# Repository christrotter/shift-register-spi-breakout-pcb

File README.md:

# Overview
Tested and working as of 20240403! \o/

A simple? breakout board that provides 32 matrix pins (_16 row and 16 column_) over SPI - using only 6 MCU pins!
Designed for and tested in QMK - requires a custom matrix.  Expects you to be using ROW2COL diode orientation.

This document includes:
- Understanding shift registers (_rather extensive_)
- Matrix-inator PCB notes
- Matrix-inator schematic detail
- Sample code

There's also a [STEP file](/matrix-inator-rev2.step) for testing fitment on your models.

*-inate your keyboard matrix with the Matrix-inator!*

# Implementation notes
- The code examples are QMK-centric and utilize Chibios bits and bobs
- The latch header is redundant - **should always be connected ("enable latch")**.  If there's a future rev I will remove it.

# Why not 74HC165 shift registers?
There are 74HC589 supply issues, why not use the 74HC165 shift register?  Because *the 165 cannot share the SPI bus*, and QMK only allows you - at present - to utilize a single SPI bus.  You could use the 165 if you also included a tri-state buffer (e.g. 74HC1G125-Q100).  The 589 has that built-in.

# Usage
After soldering/hooking this into your keyboard, you'll need to add the custom matrix code to your QMK keyboard.

Between the [QMK docs](https://docs.qmk.fm/#/custom_matrix?id=custom-matrix) and this readme, you should have enough to get off the ground.

#### Connection
You can use the included 2x4 2.54mm pin header arrangement (_fits up to JST-XH headers_), or a [VIK-format 12-pin@0.5mm pitch FPC cable](https://github.com/sadekbaroudi/vik)
- _Power_: GND, 3.3V
- _Any GPIO_: Row CS, Col CS, Latch
- _SPI_: Clock/MISO/MOSI from the same SPI bus
- _rows and cols_: 2.54mm headers, do what you want here.

#### PCBA (PCB assembly)
If you want to order this, the gerbers are included in the latest [Github release](https://github.com/christrotter/shift-register-spi-breakout-pcb/releases/latest).

I seem to recall there being a silly part showing up that shouldn't have been (_like a logo or something_), but everything important came through.

Headers not part of the BOM, only the complicated and fiddly stuff.

#### Additonal parts you'll need
See the latest [Github release](https://github.com/christrotter/shift-register-spi-breakout-pcb/releases/latest) if you need all the parts.
- (_optional_) some flavour of 2.54mm-spaced headers
- 12-pin @ 0.5mm pitch FPC cable of sufficient length and a keyboard with a VIK port
  - (_or_) 2x 4-pin 2.54mm headers
- M3 hardware or some way of mounting the pcb to your model

#### Latch header notes
There's a 3-pin header labeled **Enable Latch**.

> *It will need to have pins 2 & 3 connected for the latch to work.* 

This is a development leftover.  Future revisions will not have it.

# Understanding shift registers
In order to understand shift registers, it's very important to understand how QMK's matrix scanning works.  And, of course, to understand that, you need to read their docs:
- https://docs.qmk.fm/#/understanding_qmk
- https://docs.qmk.fm/#/how_keyboards_work
- https://docs.qmk.fm/#/how_a_matrix_works

This doc is my simplification of the topic.

> **NOTE**: for the sake of illustration, you can use the idea that HIGH = "pin has voltage" and LOW = "pin is grounded". 

## Matrix scanning, tl;dr: 
1. Start matrix scan
2. Loop over each row pin.  on each loop, set this row pin HIGH (_all others LOW_) and then check **ALL** col pins for a reciprocal HIGH.
3. Build a `new_matrix_maybe` object with the result of each row iteration
4. Compare `live_matrix` with `new_matrix_maybe` - if differences, replace `live_matrix` with `new_matrix_maybe`
5. End matrix scan loop
(_and now QMK does everything else_)

> Have you ever looked at the QMK console messages for 'scan rate'?  Well that number is how many times per second the above matrix scan runs (_simplifying_).

> **NOTE**: I use the term 'row pin' in this document only to keep things simple - QMK and shift registers don't work the same way as if you had GPIOs configured as row pins.

### why ROW2COL and not COL2ROW?
I have been working on integrating the Cyboard flex-pcb system into my latest build, and Cyboard is ROW2COL.  I'm sure the design could be refactored to handle any config method.  Indeed, if you use `direct pin` (_where the switches connect to ground_) you can have an even simpler shift register and matrix design.

If you're used to COL2ROW, it's, for all intents and purposes, identical, just flip rows & cols around.

## Pseudo matrix scan code
This is (_mostly_) not real code.
```c
bool matrix_scan_custom(matrix_row_t current_matrix[]) {
    static matrix_row_t temp_matrix[ROWS_COUNT] = {0};
    for (uint8_t row = 0; row < (ROWS_COUNT); row++) {
        set_row_high(row_pin);              // this row pin is set HIGH; any keypresses will show as HIGH on col pins
        cycle_latch_pin(latch_pin);         // prepares the col shift registers for data shipping; shift register magic
        col_state = spi_receive(col_pin);   // ship col state from shift register into the MCU as col_state
        new_matrix_maybe[row] = col_state;  // update this row of the new_matrix_maybe object with the returned col state
    }
    bool matrix_has_changed = compare_matrix(new_matrix_maybe, live_matrix);
    if (matrix_has_changed) {
        update_active_matrix(new_matrix_maybe);
    }
    return matrix_has_changed;
}
```

## Shift register magic explained
> Obviously shift registers are not magic and are completely understandable - I use the word 'magic' as an entertaining literary device.  Covering all of the detail is just too much scope for this doc.  If I can understand it, you can, too!

There are two types of registers being used here:
- 74HC589: get the HIGH/LOW state of the data pins and return via SPI ([74HC589 datasheet](https://www.onsemi.com/pdf/datasheet/mc74hc589a-d.pdf))
- 74HC595: set the data pins to a HIGH/LOW state as per instructions sent via SPI ([74HC595 datasheet](https://www.onsemi.com/pdf/datasheet/mc74hc595a-d.pdf))

The shift registers each have 8 "data" pins and a bunch of SPI/functionality pins.  
- The 589 reads 8 bits of data from the data pins in parallel, and then ships them out serially.
- The 595 takes 8 bits of data serially and applies it to the data pins in parallel.

Said another way, one accepts data from our code (_595_), the other provides data for our code (_589_).

Remember that there are no perfect solutions, and you're always making tradeoffs.  Recall we have a GPIO constraint...the shift registers get us more "GPIO" at the cost of complication.  That complication comes in the form of a parallel->serial->parallel flow.

- "Hay, row_shift_register, set a row pin to HIGH, please"
- "Okay, while that row is HIGH; col_shift_register, check all your pins - any HIGH?"
(_repeat for every row pin_)

Consider the matrix sketch above...instead of using GPIOs to send the signals to rows/cols, we use magical shift registers.

While there are some nuances for handling resets and the like - for keyboard applications you endlessly loop over rows, so no need for resets or anything fancy on the row_shift_registers.  But, the col_shift_registers handle ordered data...and if you handle the data incorrectly, your matrix results are sporadic at best.

So you need to understand a tiny bit about the 589 shift registers.

Simply put - the data we need is stored in the `data latch`.  To retrieve it via SPI, we need to tell the register to transfer it from the `data latch` into the `shift register`, which has a small amount of memory for serial operations.  Once in the next 'serial transfer' part of the clock cycling, the data in the `shift register` will be pulled out over SPI.

> Remember, the 595 works on effectively the same principles, just the reverse flow.

### Deep magicks
Each shift register has 8 bits (_1 byte_) - the data pins are digital, 0 or 1 - so you can understand what is going on in your digital matrix (_HIGH/LOW_) by polling your shift registers with sets/gets (_layman's terms_).

### for each row pin
> **NOTE**: CS pins on registers are normally HIGH.  You set them LOW to activate them.

> **NOTE**: The flow graphics illustrate how a 589 register works.  A 595 is exactly the same picture, just mirrored.

1. Set `row_cs` LOW; the rows register is now the active SPI device
2. Send the data packet telling the register which pin to set HIGH (`spi_transmit`)
3. Set `row_cs` HIGH; we are done with the rows register, so de-select it
4. Set the `latch` HIGH; the 589 register transfers current pin data from latch to register
5. Set the `latch` LOW; register cannot do data transfer while latch is HIGH
6. Set the `col_cs` LOW - the register will start transferring data over SPI
7. Get the data packet that will tell us which col pin is HIGH (`spi_receive`)
8. Set the `col_cs` HIGH - we are done with the cols register, so de-select it

And now consider the 589 data flow mentioned above...

## even more depth
...is something I won't get into.  Suffice to say that the registers function with a lot of clock timing and conditions available based on what is HIGH and what is LOW.

The matrix code, Kicad files, and part datasheets provide the rest of the puzzle.

A very important feature of the design are the 10k resistor arrays/networks that pull down the col pins to ground.  If you fail to implement this you will get super random/repeating responses.  How do I know this?

### it's complicated
The order of operations is determined by the timing diagram.  That sentence makes me sound like an elite who knows more than you.  _lies.  deception._

# Matrix-inator notes

## For the DIY-er
If you want to incorporate shift registers into your PCB, highly advise you do the following...
- Read the datasheets, carefully, twice, then thrice.
- Remember that pcb manufacturers have tolerances.  Abide by them and err on the generous side.
- The pull-down effect of the 10k resistor network is non-negotiable.  Floating signal is a guarantee, not a maybe.  Floating signal means your board does not work.
- Remember that decoupling caps need to be as close as possible to their device, and the current should flow through the cap trace into the device.

## Performance
It's worth noting that if you use the full 16 rows you will not have a very performant keyboard - scan rate drops to **1100**.  Still usable as a keyboard, but you won't have a ton of CPU overhead for other features.

## PCB details
- M3 mounts; 65mm center-to-center
- The shift registers are only available as extended parts from JLC (_extra fees_)
- 2.54mm spacing on all pin footprints
- Row/col pins designed for 4x 8-pin JST-XH 2.54 headers
- Normal 2.54mm pin headers also work fine
- Two-layer board; ground pour on both sides tied together with vias

## VIK module certification

| Category                | Classification          | Response           |
| ----------------------- | ----------------------- | ------------------ |
| FPC connector           | Required                | :heavy_check_mark: |
| Breakout pins           | Recommended             | :heavy_check_mark: |
| Uses: SPI               | Optional                | :heavy_check_mark: |
| SPI used for SPI only   | Strongly recommended    | :heavy_check_mark: |
| Uses: I2C               | Optional                | :x:                |
| I2C used for I2C only   | Strongly Recommended    | :x:                |
| I2C pull ups            | Required                | N/A                |
| Uses: RGB               | Optional                | :x:                |
| Uses: Extra GPIO 1      | Optional                | :heavy_check_mark: |
| Uses: Extra GPIO 2      | Optional                | :heavy_check_mark: |
| Standard PCB Size/Mount | Strongly recommended    | :x:                |

## Pins
- ROW_CS - trigger to enable sending bits to the Row 74HC595 shift registers
- COL_CS - trigger enable reading bits from the Col 74HC589 shift registers
- LATCH_CS - trigger to prep all Col 74HC589 shift registers for data retrieval
- SPI: crucial that you use SPI pins on the same SPI bus
  - Clock: all SPI devices need this
  - MOSI: ROW shift registers are sent data from the MCU
  - MISO: COL shift registers return data to the MCU
- 3V3, GND - expects +3.3v and a ground

## Schematics

# Sample code
This will undoubtedly get improved, but this is enough to get you off the ground and using the Matrix-inator.

## info.json
Bits you'll need in `keyboard/info.json`:
```json
    "diode_direction": "ROW2COL",
    "matrix_pins": {
        "custom_lite": true,
        "rows": ["NO_PIN", "NO_PIN", "NO_PIN", "NO_PIN", "NO_PIN", "NO_PIN"],
        "cols": ["NO_PIN", "NO_PIN", "NO_PIN", "NO_PIN", "NO_PIN", "NO_PIN", "NO_PIN", "NO_PIN", "NO_PIN", "NO_PIN", "NO_PIN"]
      },
    "layouts": {
        "LAYOUT": {
            "layout": [
                {"matrix": [5, 0], "x": 0, "y": 0},
                {"matrix": [5, 1], "x": 1, "y": 0},
                etc
        }
    },
```

## config.h
Bits you'll need in `keyboard/config.h`:

For figuring out which SPI GPIO to use, section 1.4.3 here: https://datasheets.raspberrypi.com/rp2040/rp2040-datasheet.pdf
```c
// SPI configuration
#define SPI_MATRIX_DIVISOR 16
#define SPI_MODE 0
#define SPI_DRIVER SPID1 // you might change this
// GPIO config for main SPI config needs to match up with the SPI bus you are using
#define SPI_SCK_PIN  GPxx // e.g. SPI0 SCK
#define SPI_MOSI_PIN GPxx // e.g. SPI0 TX (Master Out, Slave In)
#define SPI_MISO_PIN GPxx // e.g. SPI0 RX (Master In, Slave Out)
// GPIO config for CS/latch pins can be any GPIO
#define SPI_MATRIX_LATCH_PIN GPxx
#define SPI_MATRIX_CHIP_SELECT_PIN_ROWS GPxx
#define SPI_MATRIX_CHIP_SELECT_PIN_COLS GPxx
// custom matrix config
#define MATRIX_COLS_SHIFT_REGISTER_COUNT 2
#define MATRIX_ROWS_SHIFT_REGISTER_COUNT 2
#define ROWS_COUNT 12 // this can be replaced w. array_size or something?
#define ROWS { \
    0b0000000000000001, \
    0b0000000000000010, \
    0b0000000000000100, \
    0b0000000000001000, \
    0b0000000000010000, \
    0b0000000000100000, \
    0b0000000001000000, \
    0b0000000010000000, \
    0b0000000100000000, \
    0b0000001000000000, \
    0b0000010000000000, \
    0b0000100000000000, \
} // this makes up the magic of the 'message' we send to the 595 register
```

## rules.mk
For `keyboard/rules.mk`:
```
SRC += matrix.c
```

## halconf.h
Bits you'll need in `keyboard/halconf.h`:

```c
#define HAL_USE_SPI TRUE
#define SPI_USE_WAIT TRUE
#define SPI_SELECT_MODE SPI_SELECT_MODE_PAD
```

## mcuconf.h
Bits you'll need in `keyboard/mcuconf.h`:

You might use SPI0?
```c
#undef RP_SPI_USE_SPI1
#define RP_SPI_USE_SPI1 TRUE
```

## matrix.c
This file goes in: `keyboard/keymap/map/` (_I think it might actually be meant to go in the keymap dir?_)

Actual working code.  (_mostly tested as of this writing_)
```c
// Copyright 2018-2022 Nick Brassel (@tzarc)
// Copyright 2020-2023 alin m elena (@alinelena, @drFaustroll)
// Copyright 2023 Stefan Kerkmann (@karlk90)
// Copyright 2023 (@burkfers)
// SPDX-License-Identifier: GPL-3.0-or-later

#include "quantum.h"
#include "spi_master.h"

static const uint16_t row_values[ROWS_COUNT] = ROWS;
static const pin_t latch_pin = SPI_MATRIX_LATCH_PIN;

void matrix_init_custom(void) {
    setPinOutput(SPI_MATRIX_CHIP_SELECT_PIN_COLS);
    writePinHigh(SPI_MATRIX_CHIP_SELECT_PIN_COLS);
    setPinOutput(SPI_MATRIX_CHIP_SELECT_PIN_ROWS);
    writePinHigh(SPI_MATRIX_CHIP_SELECT_PIN_ROWS);
    setPinOutput(latch_pin);
    writePinLow(latch_pin);
    spi_init();
}

static inline void write_to_rows(uint16_t value) {
    uint8_t message[2] = {(uint8_t)(value & 0xFF), (value >> 8) & 0xFF}; // cut 0xABCD into {0xAB, 0xCD}
    spi_start(SPI_MATRIX_CHIP_SELECT_PIN_ROWS, true, SPI_MODE, SPI_MATRIX_DIVISOR);
    spi_transmit(message, 2);
    spi_stop();
}

// /**
//  * @brief Helper function to wait until a pin  has reached the wanted target
//  * state. This only works for Push-Pull pins with enabled input stage.
//  */
static void __time_critical_func(write_and_wait_for_pin)(pin_t pin, uint8_t target_state) {
    writePin(pin, target_state);
    rtcnt_t start = chSysGetRealtimeCounterX();
    rtcnt_t end   = start + MS2RTC(REALTIME_COUNTER_CLOCK, 20);
    while (chSysIsCounterWithinX(chSysGetRealtimeCounterX(), start, end)) {
        if (readPin(pin) == target_state) {
            return;
        }
    }
}

bool matrix_scan_custom(matrix_row_t current_matrix[]) {
    static matrix_row_t temp_matrix[ROWS_COUNT] = {0};
    
    for (uint8_t row = 0; row < (ROWS_COUNT); row++) {
        uint8_t temp_col_receive[MATRIX_COLS_SHIFT_REGISTER_COUNT] = {0};
        uint16_t temp_col_state;

        write_to_rows(row_values[row]);

        // get the shift registers to move data from latch to register
        write_and_wait_for_pin(latch_pin, 1);
        write_and_wait_for_pin(latch_pin, 0);

        // read the cols shift register contents over serial
        spi_start(SPI_MATRIX_CHIP_SELECT_PIN_COLS, true, SPI_MODE, SPI_MATRIX_DIVISOR);
        spi_receive((uint8_t*)temp_col_receive, MATRIX_COLS_SHIFT_REGISTER_COUNT);
        spi_stop();

        temp_col_state = temp_col_receive[0] | (temp_col_receive[1] << 8);
        temp_matrix[row] = temp_col_state;
    }
    bool matrix_has_changed = memcmp(current_matrix, temp_matrix, sizeof(temp_matrix)) != 0;
    if (matrix_has_changed) {
        memcpy(current_matrix, temp_matrix, sizeof(temp_matrix));
    }
    return matrix_has_changed;
}
```

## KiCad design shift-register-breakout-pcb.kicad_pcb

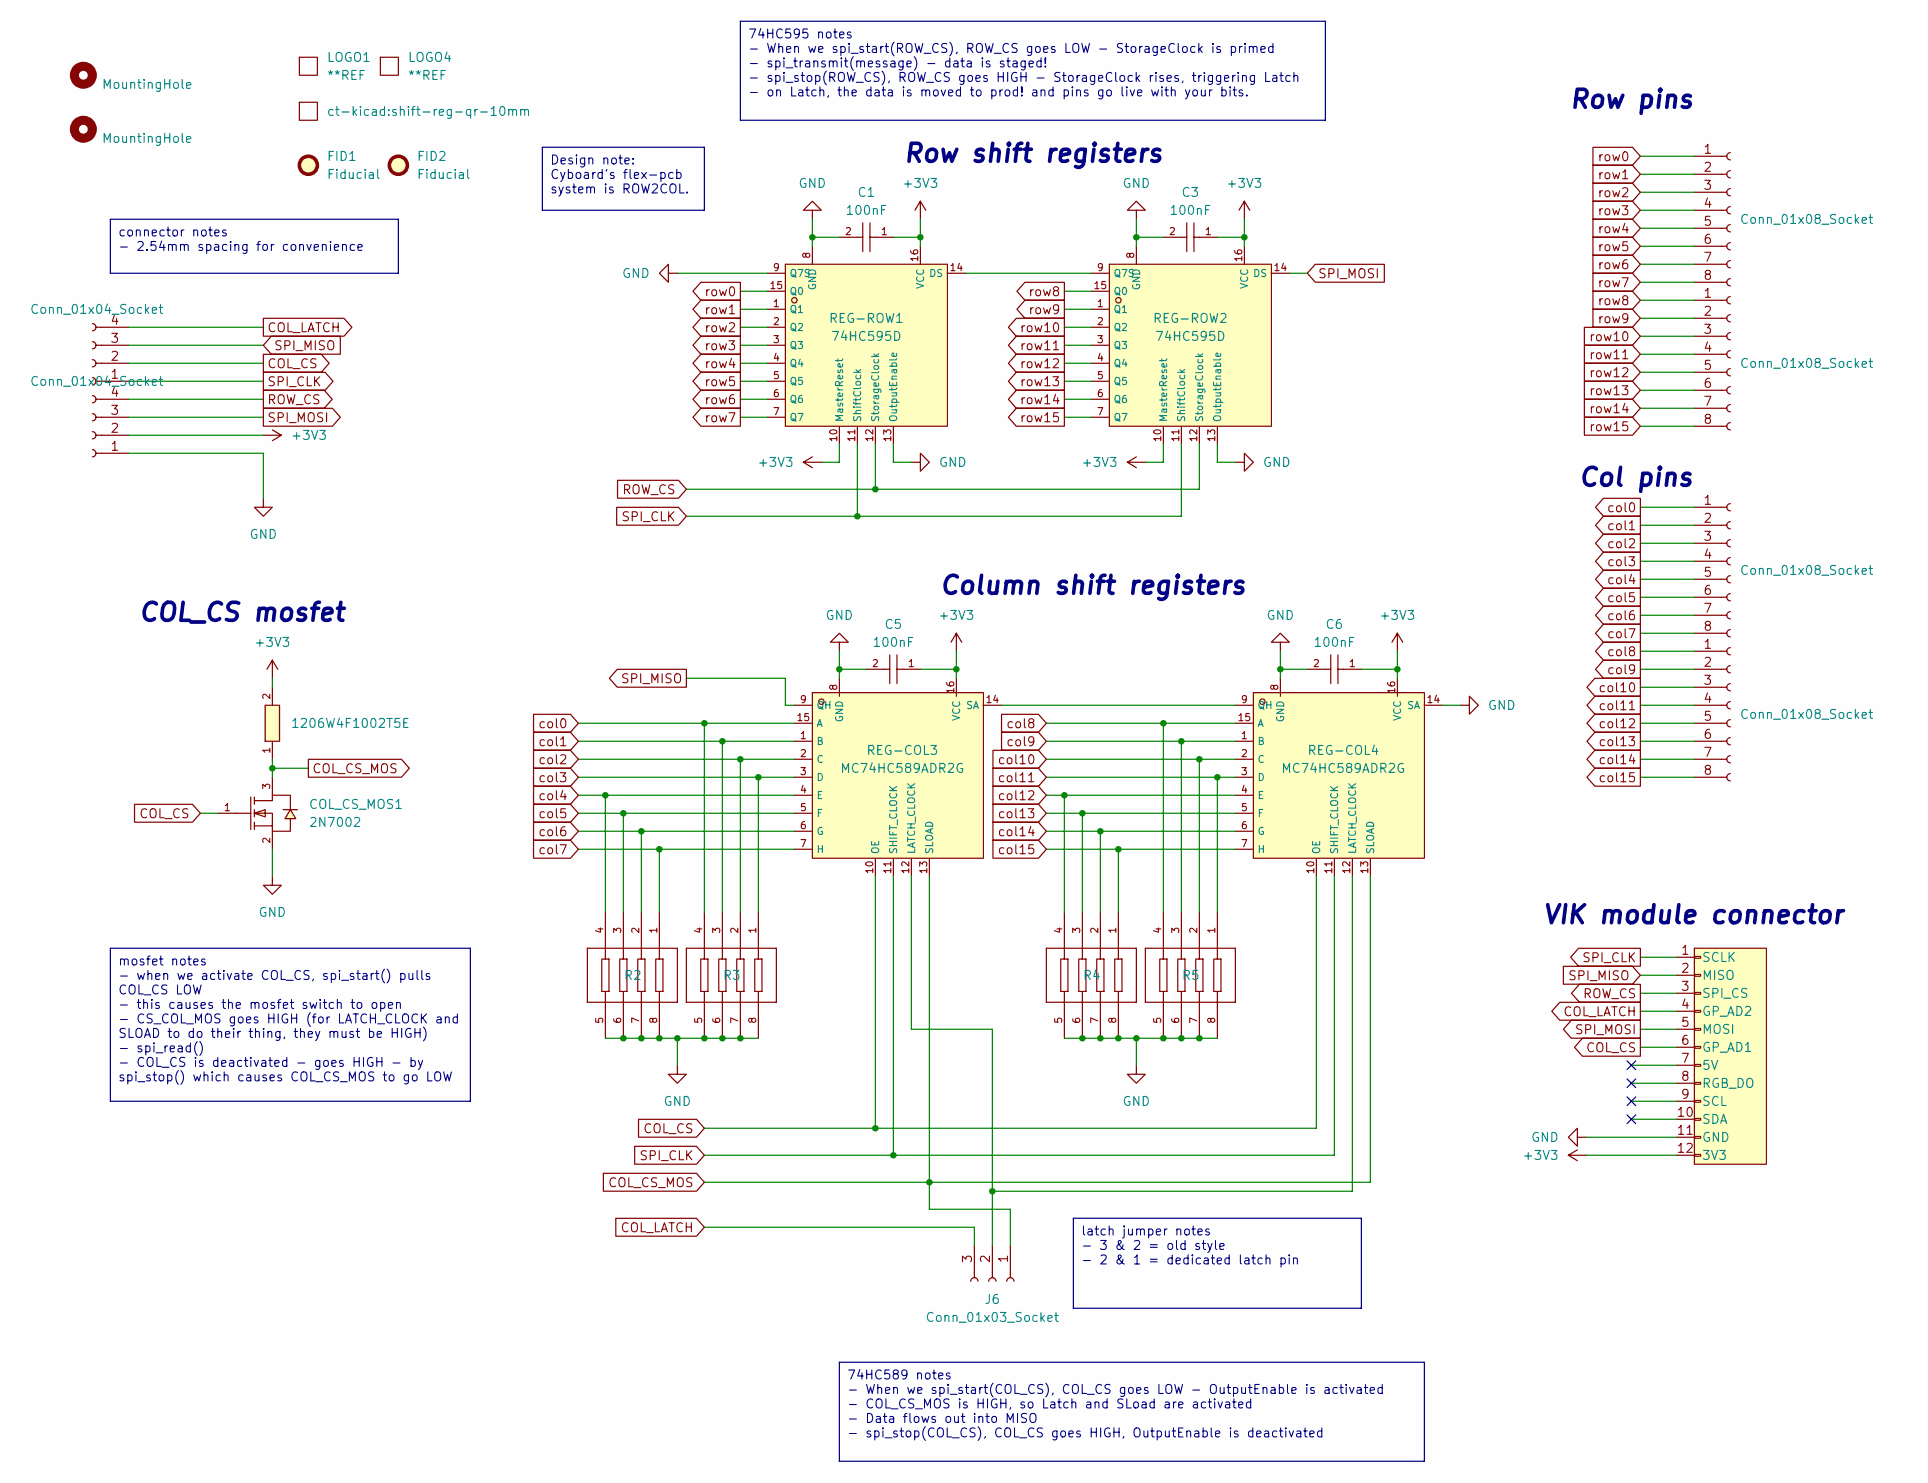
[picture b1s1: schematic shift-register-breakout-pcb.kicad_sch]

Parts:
C1, C3, C5, C6: 100nF; C0402; LCSC C1525
COL_CS_MOS1: 2N7002; SOT-23-3_L2.9-W1.3-P1.90-LS2.4-BR; LCSC C8545
FID1, FID2: Fiducial; vik-logo-small
H1, H2: MountingHole; MountingHole_3mm_Pad_Via
J1, J8: Conn_01x04_Socket; JST_XH_B4B-XH-A_1x04_P2.50mm_Vertical
J2, J3, J4, J5: Conn_01x08_Socket; JST_XH_B8B-XH-A_1x08_P2.50mm_Vertical
J6: Conn_01x03_Socket; PinHeader_1x03_P2.54mm_Vertical
J7: vik-module-connector; FPC-SMD_XF2M-1215-1AH
LOGO1, LOGO4: **REF; awesome-logo
LOGO2: **REF; shift-reg-qr-10mm
R1: 1206W4F1002T5E; R1206; LCSC C17902
R2, R3, R4, R5: 4D03WGJ0103T5E; RES-ARRAY-SMD_0603-8P-L3.2-W1.6-BL; LCSC C29718
REG-COL3, REG-COL4: MC74HC589ADR2G; SOIC-16_L9.9-W3.9-P1.27-LS6.0-BL; LCSC C7343
REG-ROW1, REG-ROW2: 74HC595D; SOIC-16_L9.9-W3.9-P1.27-LS6.0-BL; LCSC C5947

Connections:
+3V3: C1.1, C3.1, C5.1, C6.1, J7.12 (3V3), J8.2, R1.2, REG-COL3.16 (VCC), REG-COL4.16 (VCC), REG-ROW1.10 (MasterReset), REG-ROW1.16 (VCC), REG-ROW2.10 (MasterReset), REG-ROW2.16 (VCC)
COL_CS: COL_CS_MOS1.1 (G), J1.2, J7.6 (GP_AD1), REG-COL3.10 (OE), REG-COL4.10 (OE)
COL_CS_MOS: COL_CS_MOS1.3 (D), J6.1, R1.1, REG-COL3.13 (SLOAD), REG-COL4.13 (SLOAD)
COL_LATCH: J1.4, J6.3, J7.4 (GP_AD2)
GND: C1.2, C3.2, C5.2, C6.2, COL_CS_MOS1.2 (S), J7.11 (GND), J8.1, R2.5, R2.6, R2.7, R2.8, R3.5, R3.6, R3.7, R3.8, R4.5, R4.6, R4.7, R4.8, R5.5, R5.6, R5.7, R5.8, REG-COL3.8 (GND), REG-COL4.8 (GND), REG-COL4.14 (SA), REG-ROW1.8 (GND), REG-ROW1.9 (Q7S), REG-ROW1.13 (OutputEnable), REG-ROW2.8 (GND), REG-ROW2.13 (OutputEnable)
unnamed: J6.2, REG-COL3.12 (LATCH_CLOCK), REG-COL4.12 (LATCH_CLOCK)
unnamed: REG-COL3.14 (SA), REG-COL4.9 (QH)
unnamed: REG-ROW1.14 (DS), REG-ROW2.9 (Q7S)
ROW_CS: J7.3 (SPI_CS), J8.4, REG-ROW1.12 (StorageClock), REG-ROW2.12 (StorageClock)
SPI_CLK: J1.1, J7.1 (SCLK), REG-COL3.11 (SHIFT_CLOCK), REG-COL4.11 (SHIFT_CLOCK), REG-ROW1.11 (ShiftClock), REG-ROW2.11 (ShiftClock)
SPI_MISO: J1.3, J7.2 (MISO), REG-COL3.9 (QH)
SPI_MOSI: J7.5 (MOSI), J8.3, REG-ROW2.14 (DS)
col0: J4.1, R3.4, REG-COL3.15 (A)
col1: J4.2, R3.3, REG-COL3.1 (B)
col2: J4.3, R3.2, REG-COL3.2 (C)
col3: J4.4, R3.1, REG-COL3.3 (D)
col4: J4.5, R2.4, REG-COL3.4 (E)
col5: J4.6, R2.3, REG-COL3.5 (F)
col6: J4.7, R2.2, REG-COL3.6 (G)
col7: J4.8, R2.1, REG-COL3.7 (H)
col8: J5.1, R5.4, REG-COL4.15 (A)
col9: J5.2, R5.3, REG-COL4.1 (B)
col10: J5.3, R5.2, REG-COL4.2 (C)
col11: J5.4, R5.1, REG-COL4.3 (D)
col12: J5.5, R4.4, REG-COL4.4 (E)
col13: J5.6, R4.3, REG-COL4.5 (F)
col14: J5.7, R4.2, REG-COL4.6 (G)
col15: J5.8, R4.1, REG-COL4.7 (H)
row0: J2.1, REG-ROW1.15 (Q0)
row1: J2.2, REG-ROW1.1 (Q1)
row2: J2.3, REG-ROW1.2 (Q2)
row3: J2.4, REG-ROW1.3 (Q3)
row4: J2.5, REG-ROW1.4 (Q4)
row5: J2.6, REG-ROW1.5 (Q5)
row6: J2.7, REG-ROW1.6 (Q6)
row7: J2.8, REG-ROW1.7 (Q7)
row8: J3.1, REG-ROW2.15 (Q0)
row9: J3.2, REG-ROW2.1 (Q1)
row10: J3.3, REG-ROW2.2 (Q2)
row11: J3.4, REG-ROW2.3 (Q3)
row12: J3.5, REG-ROW2.4 (Q4)
row13: J3.6, REG-ROW2.5 (Q5)
row14: J3.7, REG-ROW2.6 (Q6)
row15: J3.8, REG-ROW2.7 (Q7)

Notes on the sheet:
mosfet notes - when we activate COL_CS, spi_start() pulls COL_CS LOW - this causes the mosfet switch to open - CS_COL_MOS goes HIGH (for LATCH_CLOCK and SLOAD to do their thing, they must be HIGH) - spi_read() - COL_CS is deactivated - goes HIGH - by spi_stop() which causes COL_CS_MOS to go LOW
74HC595 notes - When we spi_start(ROW_CS), ROW_CS goes LOW - StorageClock is primed - spi_transmit(message) - data is staged! - spi_stop(ROW_CS), ROW_CS goes HIGH - StorageClock rises, triggering Latch - on Latch, the data is moved to prod! and pins go live with your bits.
74HC589 notes - When we spi_start(COL_CS), COL_CS goes LOW - OutputEnable is activated - COL_CS_MOS is HIGH, so Latch and SLoad are activated - Data flows out into MISO - spi_stop(COL_CS), COL_CS goes HIGH, OutputEnable is deactivated
Design note: Cyboard's flex-pcb system is ROW2COL.
connector notes - 2.54mm spacing for convenience
latch jumper notes - 3 & 2 = old style - 2 & 1 = dedicated latch pin
Column shift registers
COL_CS mosfet
Col pins
Row pins
Row shift registers
VIK module connector

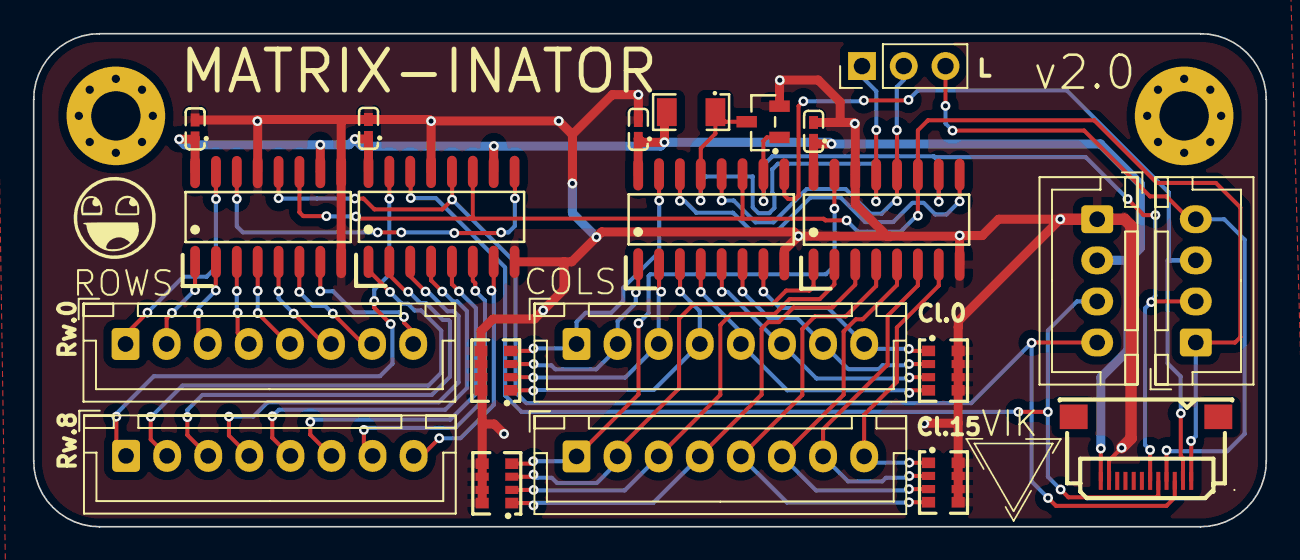
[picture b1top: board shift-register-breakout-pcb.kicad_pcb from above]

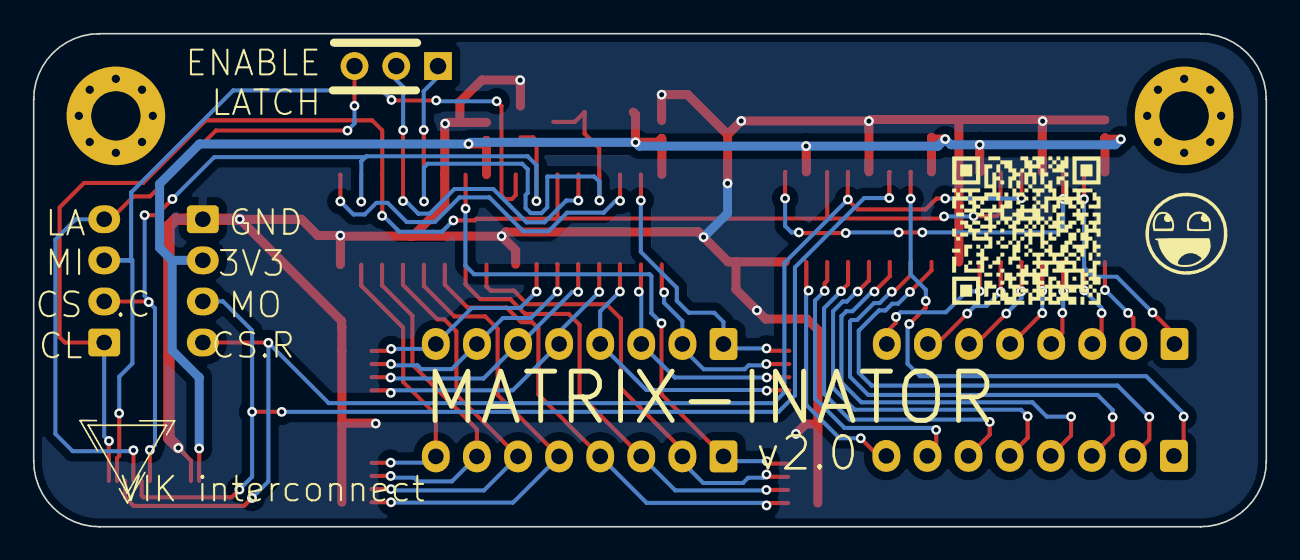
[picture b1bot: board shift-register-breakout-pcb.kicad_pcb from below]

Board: 2 copper layers, 75.0 x 30.0 mm, 29 parts (3 on the bottom side), 44 nets.

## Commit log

2024-01-07 v1.0 of the breakout board - need to figure out how to properly do logo symbols.
2024-01-07 adding text, fixing some errors.
2024-01-07 fixing mosfet notes in schematic as per burkfers, final pcb notation added
2024-01-07 updating readme with details
2024-01-07 wups forgot the pic
2024-03-05 adding latch circuit and resistor arrays
2024-03-05 some silkscreen and other changes
2024-03-06 vik-i-fying the design
2024-03-06 has been suggested to minimize the design...
2024-03-07 mostly done vik-ifying it
2024-03-07 final vik version
2024-03-10 adding images
2024-03-10 almost done readme
2024-03-10 adding step file for easy preview
2024-03-10 added step note
2024-03-10 correcting error with hi/lo comments for cs pins
2024-03-10 bunch of fixes and additions
2024-03-10 more updates
2024-03-10 step file link
2024-03-11 Adding VIK certification to README.md
2024-03-11 updating w. some burkfers suggestions
2024-03-11 more rewording
2024-03-11 formatting
2024-04-04 Update README.md
    Working hardware!
    Added notes about 165, and the latch implementation. Also updated the code example to include everything you'd need.
